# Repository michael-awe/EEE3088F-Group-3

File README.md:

# EEE3088F Project (Group 3)

This GitHub repository contains the source code and documentation for a sound and proximity light sensing HAT (Hardware Attached on Top) designed for an STM32F05C6T6 Discovery board. The repository contains detailed technical documentation with diagrams, schematics and specifications for the HAT's hardware and software.

## Project Description
Our HAT (Hardware Attached on Top) is a compact device that incorporates light proximity sensor and a sound sensor, making it an all-in-one solution for non-contact detection and monitoring. Designed to work seamlessly with STM 32 microcontrollers, the HAT offers both motion and sound sensing capabilities that make it an ideal choice for a wide range of use cases such as process monitoring, home automation, surveillance, and non-contact activation.  
With an onboard battery, the HAT can operate remotely for extended periods, providing reliable and accurate data capture during load-shedding. The HAT's data capture capabilities are enhanced by its micro-USB data transfer, which allows users to easily power the microcontroller and transfer data between it and a computer. Overall, the HAT is an excellent option for businesses and organizations looking for a cost-effective, reliable, and adaptable solution for non-contact detection and monitoring. 

## Team Members
1. Michael Awe (Microcontroller interfacing + Coding)
2. Adrian Mc Intosh (Sensor Module)
3. Simon Carthew (Power Module)

## License

This repository is licensed under the Creative Commons Attribution 4.0 International license. See `LICENSE.md` for more information.

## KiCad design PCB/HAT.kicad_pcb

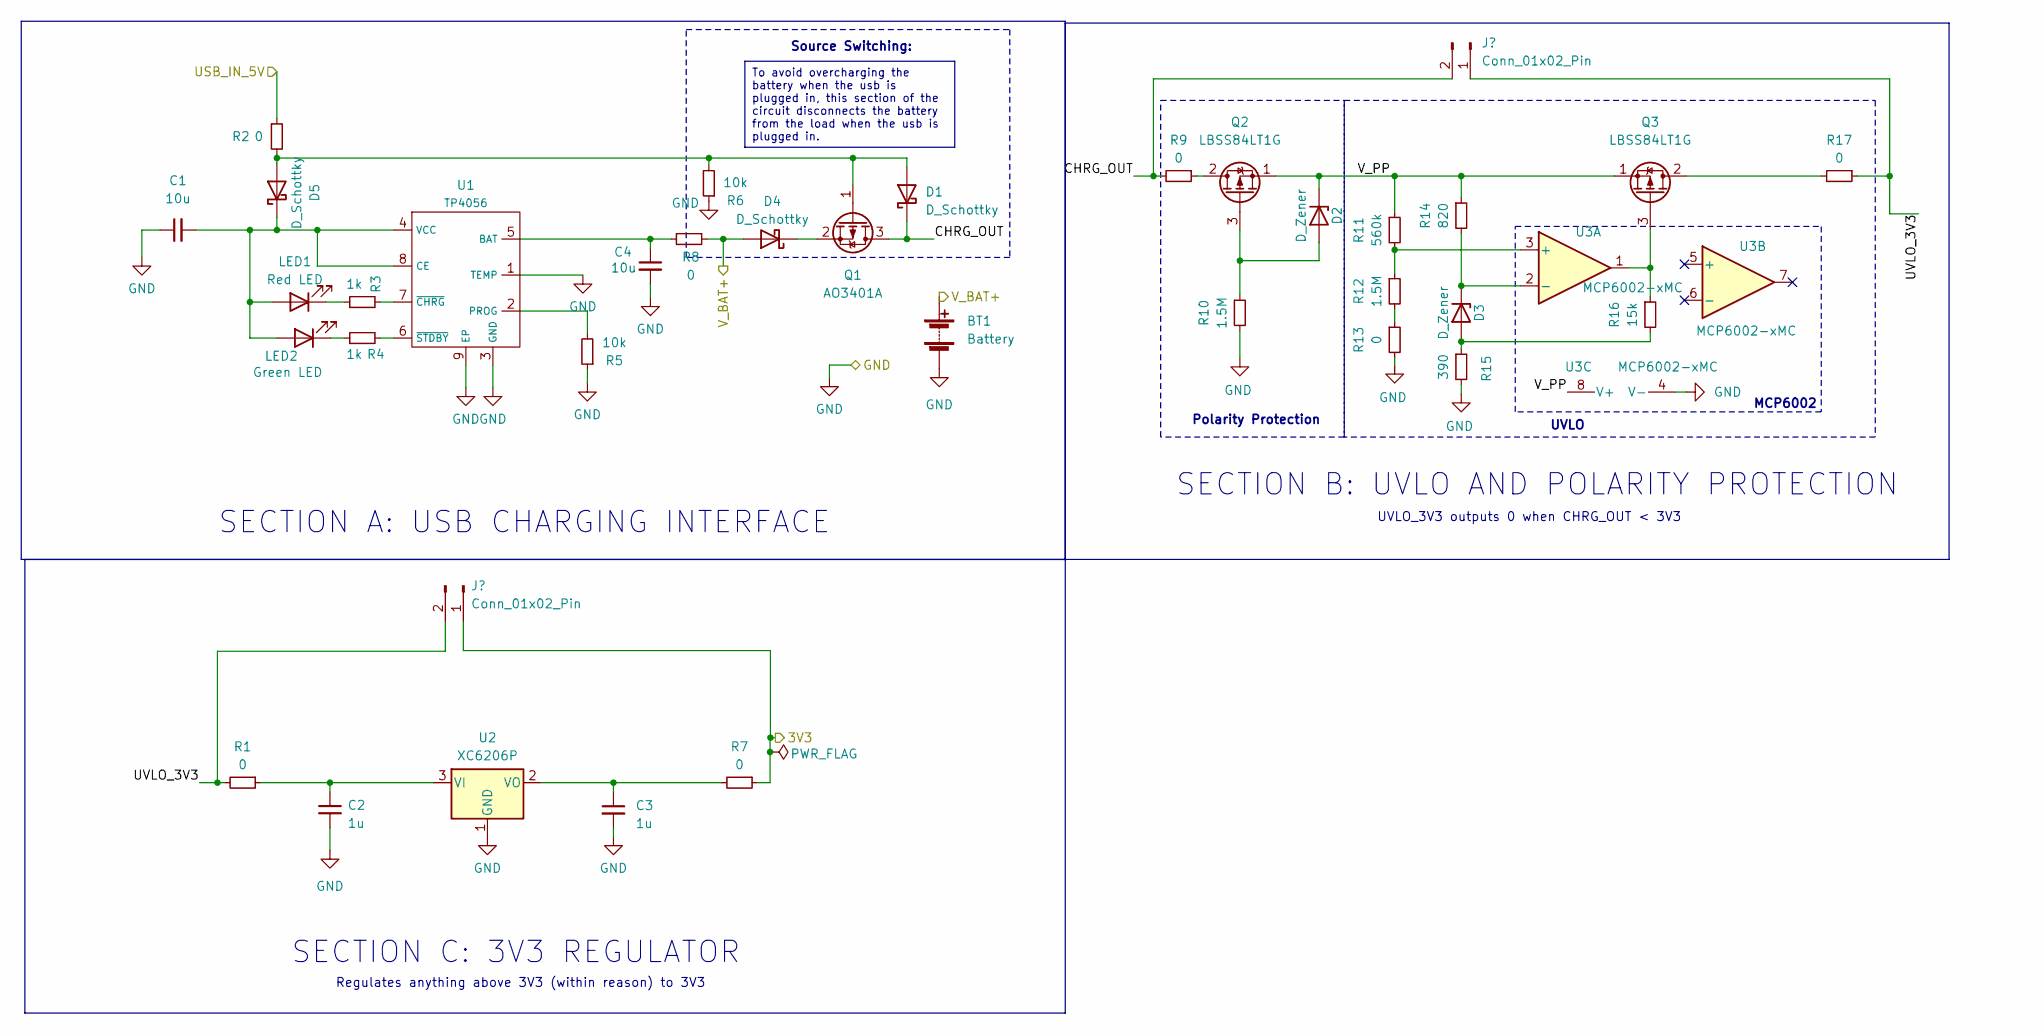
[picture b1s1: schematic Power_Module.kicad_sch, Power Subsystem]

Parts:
BT1: Battery; 18650_Holder_SMD
C1, C4: 10u; CAP-SMD_L3.2-W1.6-RD-C7171
C2, C3: 1u; C0402_NEW
D1, D4, D5: D_Schottky; SOD-323_L1.8-W1.3-LS2.5-RD
D2, D3: D_Zener; LL-34_L3.5-W1.5-RD
J1, J2: Conn_01x02_Pin; PinHeader_1x02_P2.54mm_Vertical
LED1: Red LED; LED0603-RD
LED2: Green LED; LED0805-R-RD
Q1: AO3401A; SOT-23
Q2, Q3: LBSS84LT1G; SOT-23_L2.9-W1.3-P1.90-LS2.4-BR
R1, R2, R7, R8, R9, R13, R17: 0; R_0805_2012Metric
R3, R4: 1k; R_0805_2012Metric
R5, R6: 10k; R_0805_2012Metric
R10: 1.5M; R_0805_2012Metric
R11: 560k; R_0603_1608Metric
R12: 1.5M; R_0603_1608Metric
R14: 820; R_0805_2012Metric
R15: 390; R_0805_2012Metric
R16: 15k; R_0805_2012Metric
U1: TP4056; SOIC-8-1EP_3.9x4.9mm_P1.27mm_EP2.29x3mm
U2: XC6206P; SOT-23-3
U3: MCP6002-xMC; DFN-8-1EP_3x2mm_P0.5mm_EP1.75x1.45mm

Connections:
/MicroController_Interfacing/3V3: J1.1, R7.1; also elsewhere on the board
/MicroController_Interfacing/USB 5V: R2.1; also elsewhere on the board
/Power Module/CHRG_OUT: D1.1 (K), J2.2, Q1.3 (D), R9.2
/Power Module/UVLO_3V3: J1.2, J2.1, R1.2, R17.1
/Power Module/V_BAT+: BT1.1 (+), D4.2 (A), R8.1; also elsewhere on the board
/Power Module/V_PP: D2.1 (K), Q2.1 (S), Q3.1 (S), R11.1, R14.1, U3.8 (V+)
GND: BT1.2 (-), C1.1, C2.2, C3.2, C4.2, R5.1, R6.1, R10.2, R13.2, R15.2, U1.1 (TEMP), U1.3 (GND), U1.9 (EP), U2.1 (GND), U3.4 (V-), U3.9 (V-); also elsewhere on the board
unnamed: D1.2 (A), D5.2 (A), Q1.1 (G), R2.2, R6.2
unnamed: D2.2 (A), Q2.3 (G), R10.1
unnamed: D3.2 (A), R15.1, R16.2
unnamed: D3.1 (K), R14.2, U3.2 (-)
unnamed: D4.1 (K), Q1.2 (S)
unnamed: C1.2, D5.1 (K), LED1.2 (A), LED2.2 (A), U1.4 (VCC), U1.8 (CE)
unnamed: LED1.1 (K), R3.1
unnamed: LED2.1 (K), R4.1
unnamed: Q2.2 (D), R9.1
unnamed: Q3.2 (D), R17.2
unnamed: Q3.3 (G), R16.1, U3.1
unnamed: R12.2, R13.1
unnamed: C4.1, R8.2, U1.5 (BAT)
unnamed: R5.2, U1.2 (PROG)
unnamed: R3.2, U1.7 (~CHRG)
unnamed: R4.2, U1.6 (~STDBY)
unnamed: C2.1, R1.1, U2.3 (VI)
unnamed: C3.1, R7.2, U2.2 (VO)
unnamed: R11.2, R12.1, U3.3 (+)

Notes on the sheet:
To avoid overcharging the battery when the usb is plugged in, this section of the circuit disconnects the battery from the load when the usb is plugged in.
Source Switching:
MCP6002
SECTION C: 3V3 REGULATOR
UVLO
SECTION B: UVLO AND POLARITY PROTECTION
SECTION A: USB CHARGING INTERFACE
UVLO_3V3 outputs 0 when CHRG_OUT < 3V3
Regulates anything above 3V3 (within reason) to 3V3
Polarity Protection

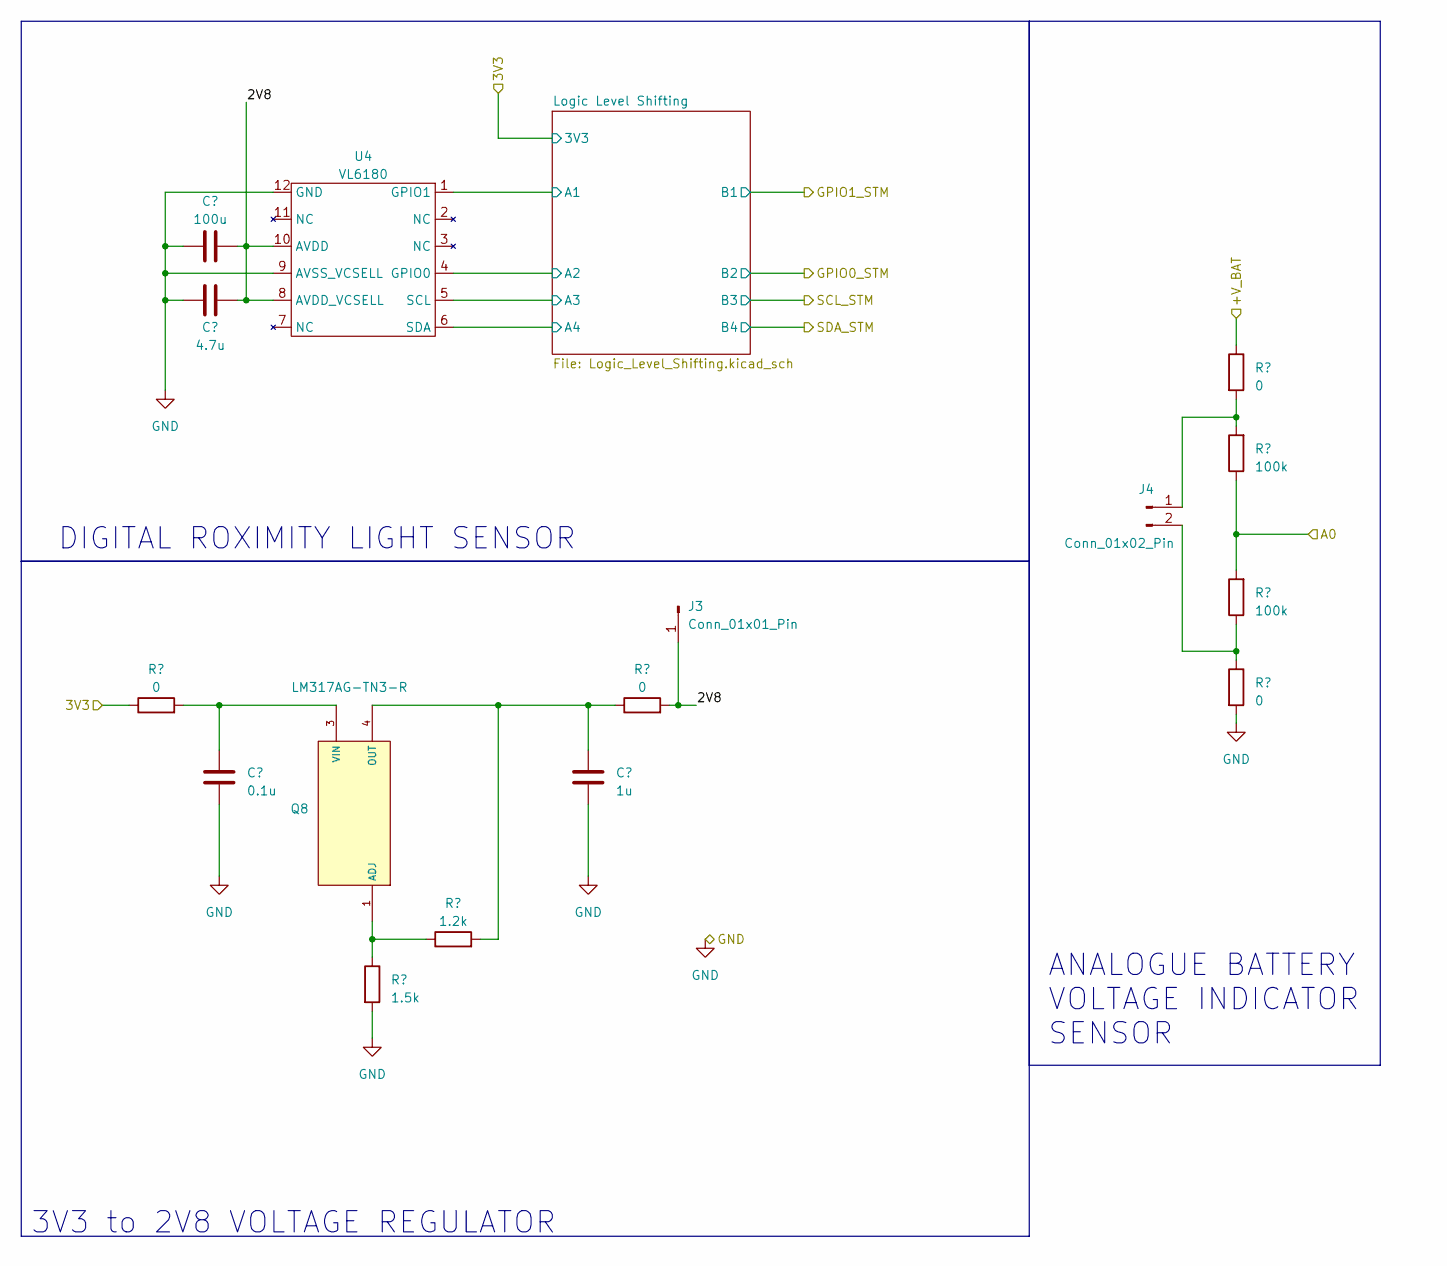
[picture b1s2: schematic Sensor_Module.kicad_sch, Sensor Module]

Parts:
C6: 100u; C1206
C7: 4.7u; C0603
C8: 0.1u; C0805
C9: 1u; C0402_NEW
J3: Conn_01x01_Pin; PinHeader_1x01_P2.54mm_Vertical
J4: Conn_01x02_Pin; PinHeader_1x02_P2.54mm_Vertical
Q8: LM317AG-TN3-R; TO-252-2_L6.5-W6.1-P4.58-LS10.0-TL; LCSC C75510
R18, R21, R22, R25: 0; R_0805_2012Metric
R19: 1.5k; R_0805_2012Metric
R20: 1.2k; R_0805_2012Metric
R23, R24: 100k; R_0805_2012Metric
U4: VL6180; LGA-12_L4.8-W2.8-P0.75-BL

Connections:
/MicroController_Interfacing/3V3: R18.1; also elsewhere on the board
/MicroController_Interfacing/A0: R23.1, R24.2; also elsewhere on the board
/Power Module/V_BAT+: R22.1; also elsewhere on the board
/Sensor Module/2V8: C6.1, C7.1, J3.1, R21.2, U4.8 (AVDD_VCSELL), U4.10 (AVDD)
/Sensor Module/Logic Level Shifting/A1: U4.1 (GPIO1); also elsewhere on the board
/Sensor Module/Logic Level Shifting/A2: U4.4 (GPIO0); also elsewhere on the board
/Sensor Module/Logic Level Shifting/A3: U4.5 (SCL); also elsewhere on the board
/Sensor Module/Logic Level Shifting/A4: U4.6 (SDA); also elsewhere on the board
GND: C6.2, C7.2, C8.1, C9.1, R19.2, R25.2, U4.9 (AVSS_VCSELL), U4.12 (GND); also elsewhere on the board
unnamed: J4.1, R22.2, R23.2
unnamed: J4.2, R24.1, R25.1
unnamed: Q8.1 (ADJ), R19.1, R20.1
unnamed: C9.2, Q8.4 (OUT), R20.2, R21.1
unnamed: C8.2, Q8.3 (VIN), R18.2

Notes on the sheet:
ANALOGUE BATTERY VOLTAGE INDICATOR SENSOR
DIGITAL ROXIMITY LIGHT SENSOR
3V3 to 2V8 VOLTAGE REGULATOR

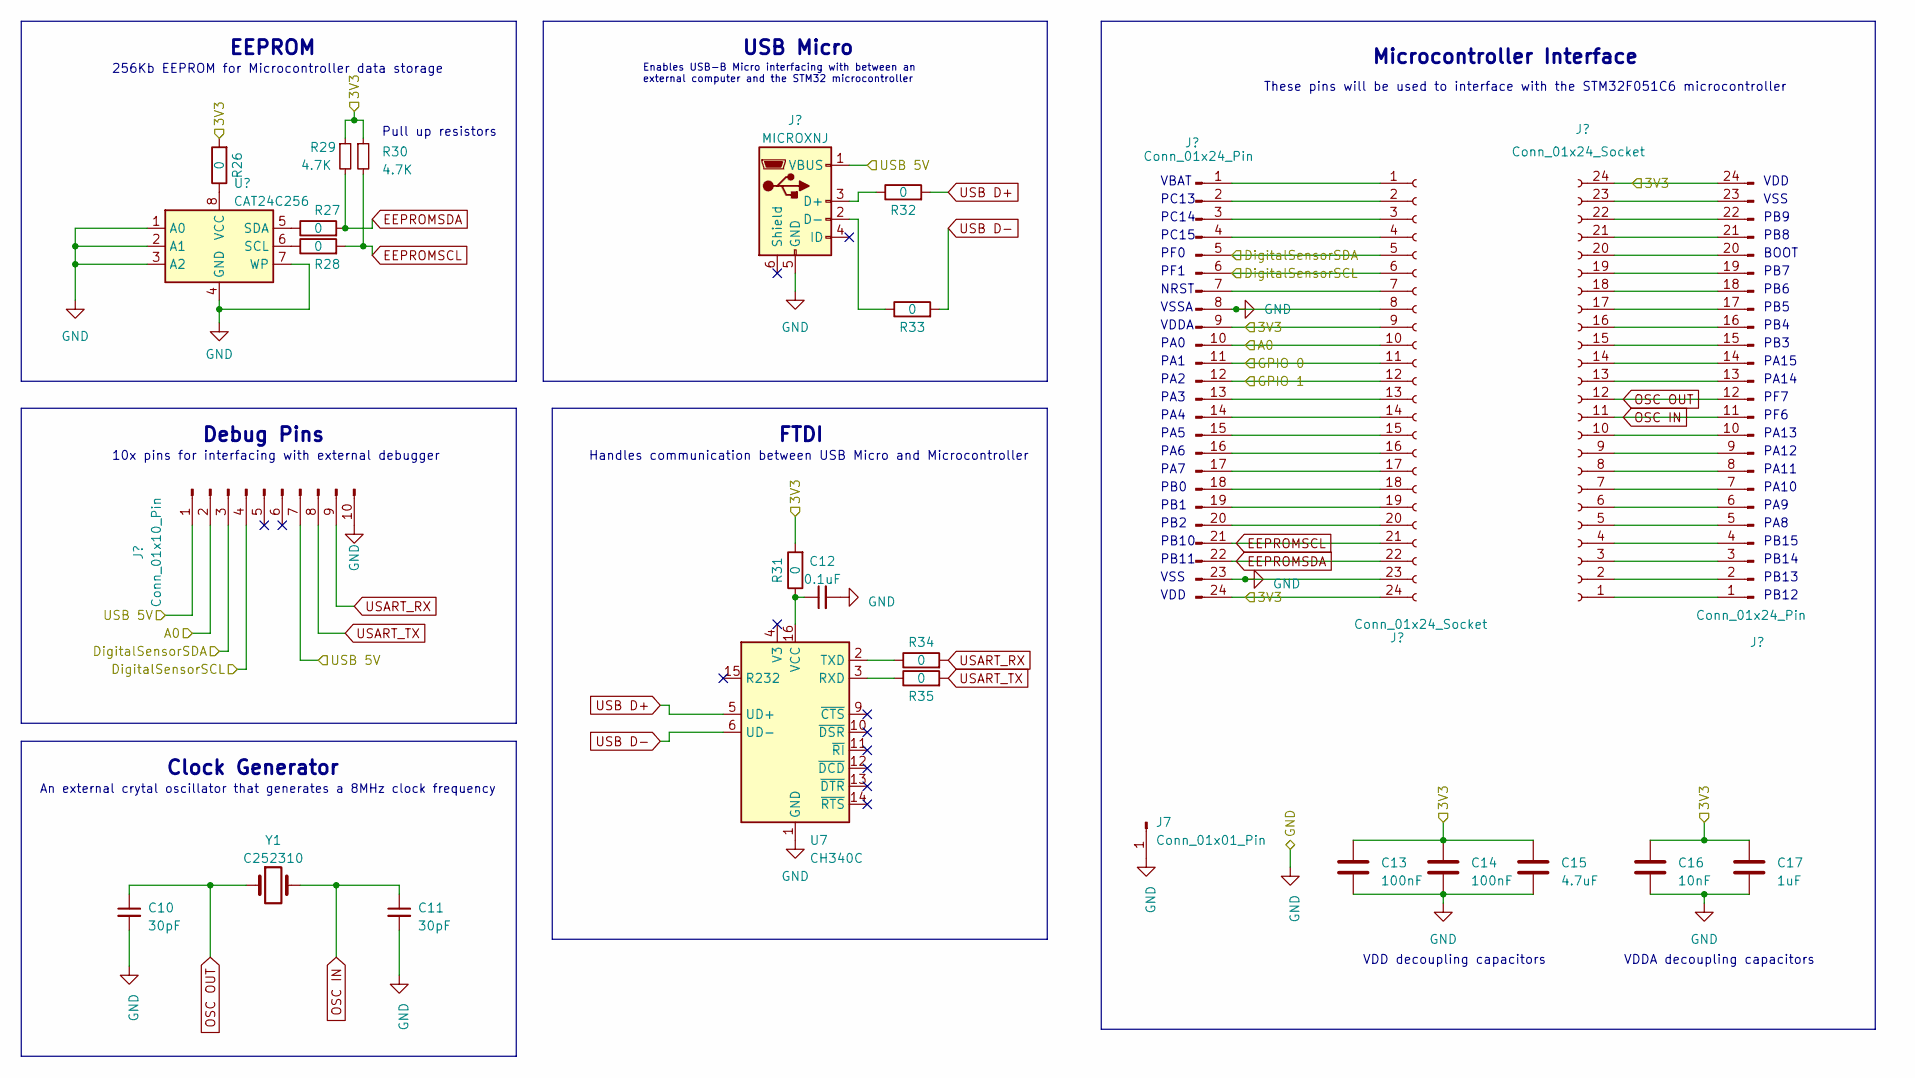
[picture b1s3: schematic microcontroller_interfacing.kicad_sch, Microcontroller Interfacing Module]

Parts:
C10, C11: 30pF; C0805
C12: 0.1uF; C0805
C13, C14: 100nF; C0402
C15: 4.7uF; C0603
C16: 10nF; C0402_NEW
C17: 1uF; C0402_NEW
J5: Conn_01x10_Pin; PinHeader_1x10_P2.54mm_Vertical
J6: MICROXNJ; USB_Conn_JLC_LCSC_C404969
J7: Conn_01x01_Pin; PinHeader_1x01_P2.54mm_Vertical
J8, J11: Conn_01x24_Pin; PinHeader_1x24_P2.54mm_Vertical
J9, J10: Conn_01x24_Socket; PinSocket_1x24_P2.54mm_Vertical
R26, R27, R28, R31, R32, R33, R34, R35: 0; R_0805_2012Metric
R29, R30: 4.7K; R_0805_2012Metric
U6: CAT24C256; SOIC-8_L4.9-W3.9-P1.27-LS6.0-BL
U7: CH340C; SOIC-16_3.9x9.9mm_P1.27mm
Y1: C252310; HC-49S_L11.4-W4.8

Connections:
/MicroController_Interfacing/3V3: C13.1, C14.1, C15.1, C16.1, C17.1, J8.9, J8.24, J9.9, J9.24, J10.24, J11.24, R26.2, R29.1, R30.1, R31.2; also elsewhere on the board
/MicroController_Interfacing/A0: J5.2, J8.10, J9.10; also elsewhere on the board
/MicroController_Interfacing/DigitalSensorSCL: J5.4, J8.6, J9.6; also elsewhere on the board
/MicroController_Interfacing/DigitalSensorSDA: J5.3, J8.5, J9.5; also elsewhere on the board
/MicroController_Interfacing/GPIO 0: J8.11, J9.11; also elsewhere on the board
/MicroController_Interfacing/GPIO 1: J8.12, J9.12; also elsewhere on the board
/MicroController_Interfacing/USB 5V: J5.1, J5.7, J6.1 (VBUS); also elsewhere on the board
EEPROMSCL: J8.21, J9.21, R28.2, R30.2
EEPROMSDA: J8.22, J9.22, R27.2, R29.2
GND: C10.2, C11.2, C12.2, C13.2, C14.2, C15.2, C16.2, C17.2, J5.10, J6.5 (GND), J7.1, J8.8, J8.23, J9.8, J9.23, U6.1 (A0), U6.2 (A1), U6.3 (A2), U6.4 (GND), U6.7 (WP), U7.1 (GND); also elsewhere on the board
unnamed: J6.3 (D+), R32.1
unnamed: J6.2 (D-), R33.1
unnamed: J8.1, J9.1
unnamed: J8.2, J9.2
unnamed: J8.3, J9.3
unnamed: J8.4, J9.4
unnamed: J8.7, J9.7
unnamed: J8.13, J9.13
unnamed: J8.14, J9.14
unnamed: J8.15, J9.15
unnamed: J8.16, J9.16
unnamed: J8.17, J9.17
unnamed: J8.18, J9.18
unnamed: J8.19, J9.19
unnamed: J8.20, J9.20
unnamed: J10.1, J11.1
unnamed: J10.2, J11.2
unnamed: J10.3, J11.3
unnamed: J10.4, J11.4
unnamed: J10.5, J11.5
unnamed: J10.6, J11.6
unnamed: J10.7, J11.7
unnamed: J10.8, J11.8
unnamed: J10.9, J11.9
unnamed: J10.10, J11.10
unnamed: J10.13, J11.13
unnamed: J10.14, J11.14
unnamed: J10.15, J11.15
unnamed: J10.16, J11.16
unnamed: J10.17, J11.17
unnamed: J10.18, J11.18
unnamed: J10.19, J11.19
unnamed: J10.20, J11.20
unnamed: J10.21, J11.21
unnamed: J10.22, J11.22
unnamed: J10.23, J11.23
unnamed: R28.1, U6.6 (SCL)
unnamed: R27.1, U6.5 (SDA)
unnamed: R26.1, U6.8 (VCC)
unnamed: R35.1, U7.3 (RXD)
unnamed: R34.1, U7.2 (TXD)
unnamed: C12.1, R31.1, U7.16 (VCC)
OSC IN: C11.1, J10.11, J11.11, Y1.2
OSC OUT: C10.1, J10.12, J11.12, Y1.1
USART_RX: J5.9, R34.2
USART_TX: J5.8, R35.2
USB D+: R32.2, U7.5 (UD+)
USB D-: R33.2, U7.6 (UD-)

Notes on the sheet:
BOOT
PA4
PB6
PA14
PB3
PA2
Microcontroller Interface
PB10
VSSA
VSS
VDD
VBAT
PC13
PF1
PA11
Clock Generator
256Kb EEPROM for Microcontroller data storage
NRST
10x pins for interfacing with external debugger
PA12
PF0
VDDA
USB Micro
PB0
PA8
PA13
PA15
PA7
PA9
Pull up resistors
PA5
PC15
These pins will be used to interface with the STM32F051C6 microcontroller
PB4
PA3
PB11
Handles communication between USB Micro and Microcontroller
PB12
PC14
An external crytal oscillator that generates a 8MHz clock frequency

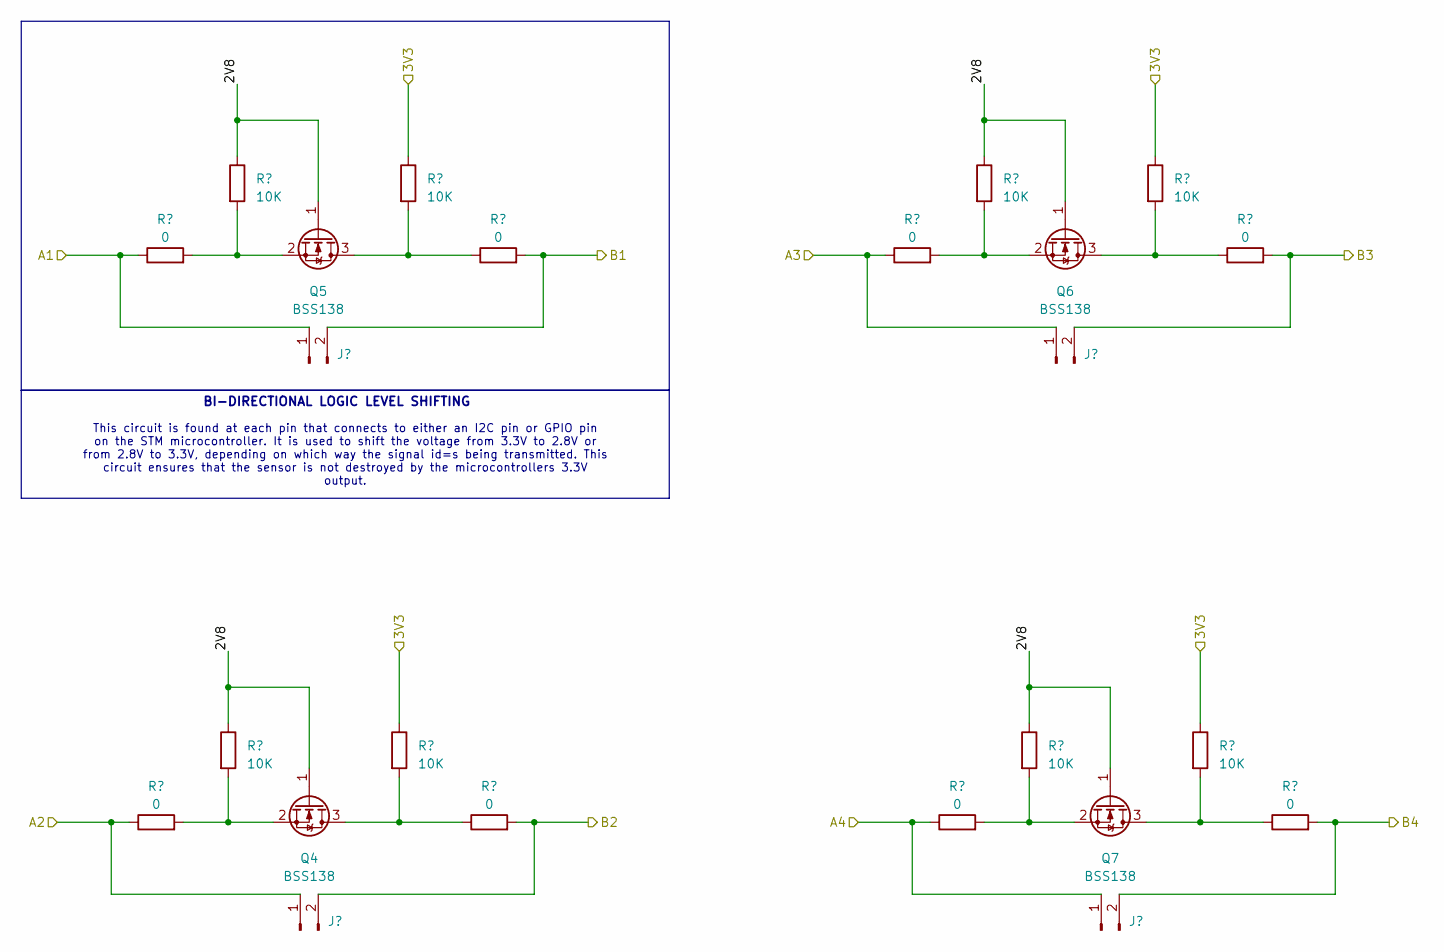
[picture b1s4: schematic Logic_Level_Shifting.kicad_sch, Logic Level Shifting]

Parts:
J12, J13, J14, J15: Conn_01x02_Pin; PinHeader_1x02_P2.54mm_Vertical
Q4, Q5, Q6, Q7: BSS138; SOT-23-3_L2.9-W1.3-P1.90-LS2.4-BR
R36, R37, R42, R43, R44, R45, R50, R51: 0; R_0805_2012Metric
R38, R39, R40, R41, R46, R47, R48, R49: 10K; R_0805_2012Metric

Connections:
/MicroController_Interfacing/3V3: R40.1, R41.1, R48.1, R49.1; also elsewhere on the board
/MicroController_Interfacing/DigitalSensorSCL: J14.2, R50.2; also elsewhere on the board
/MicroController_Interfacing/DigitalSensorSDA: J15.2, R51.2; also elsewhere on the board
/MicroController_Interfacing/GPIO 0: J12.2, R42.2; also elsewhere on the board
/MicroController_Interfacing/GPIO 1: J13.2, R43.2; also elsewhere on the board
/Sensor Module/Logic Level Shifting/2V8: Q4.1 (G), Q5.1 (G), Q6.1 (G), Q7.1 (G), R38.1, R39.1, R46.1, R47.1
/Sensor Module/Logic Level Shifting/A1: J13.1, R37.1; also elsewhere on the board
/Sensor Module/Logic Level Shifting/A2: J12.1, R36.1; also elsewhere on the board
/Sensor Module/Logic Level Shifting/A3: J14.1, R44.1; also elsewhere on the board
/Sensor Module/Logic Level Shifting/A4: J15.1, R45.1; also elsewhere on the board
unnamed: Q4.3 (D), R40.2, R42.1
unnamed: Q4.2 (S), R36.2, R38.2
unnamed: Q5.3 (D), R41.2, R43.1
unnamed: Q5.2 (S), R37.2, R39.2
unnamed: Q6.3 (D), R48.2, R50.1
unnamed: Q6.2 (S), R44.2, R46.2
unnamed: Q7.3 (D), R49.2, R51.1
unnamed: Q7.2 (S), R45.2, R47.2

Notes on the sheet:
This circuit is found at each pin that connects to either an I2C pin or GPIO pin on the STM microcontroller. It is used to shift the voltage from 3.3V to 2.8V or from 2.8V to 3.3V, depending on which way the signal id=s being transmitted. This circuit ensures that the sensor is not destroyed by the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
BI-DIRECTIONAL LOGIC LEVEL SHIFTING

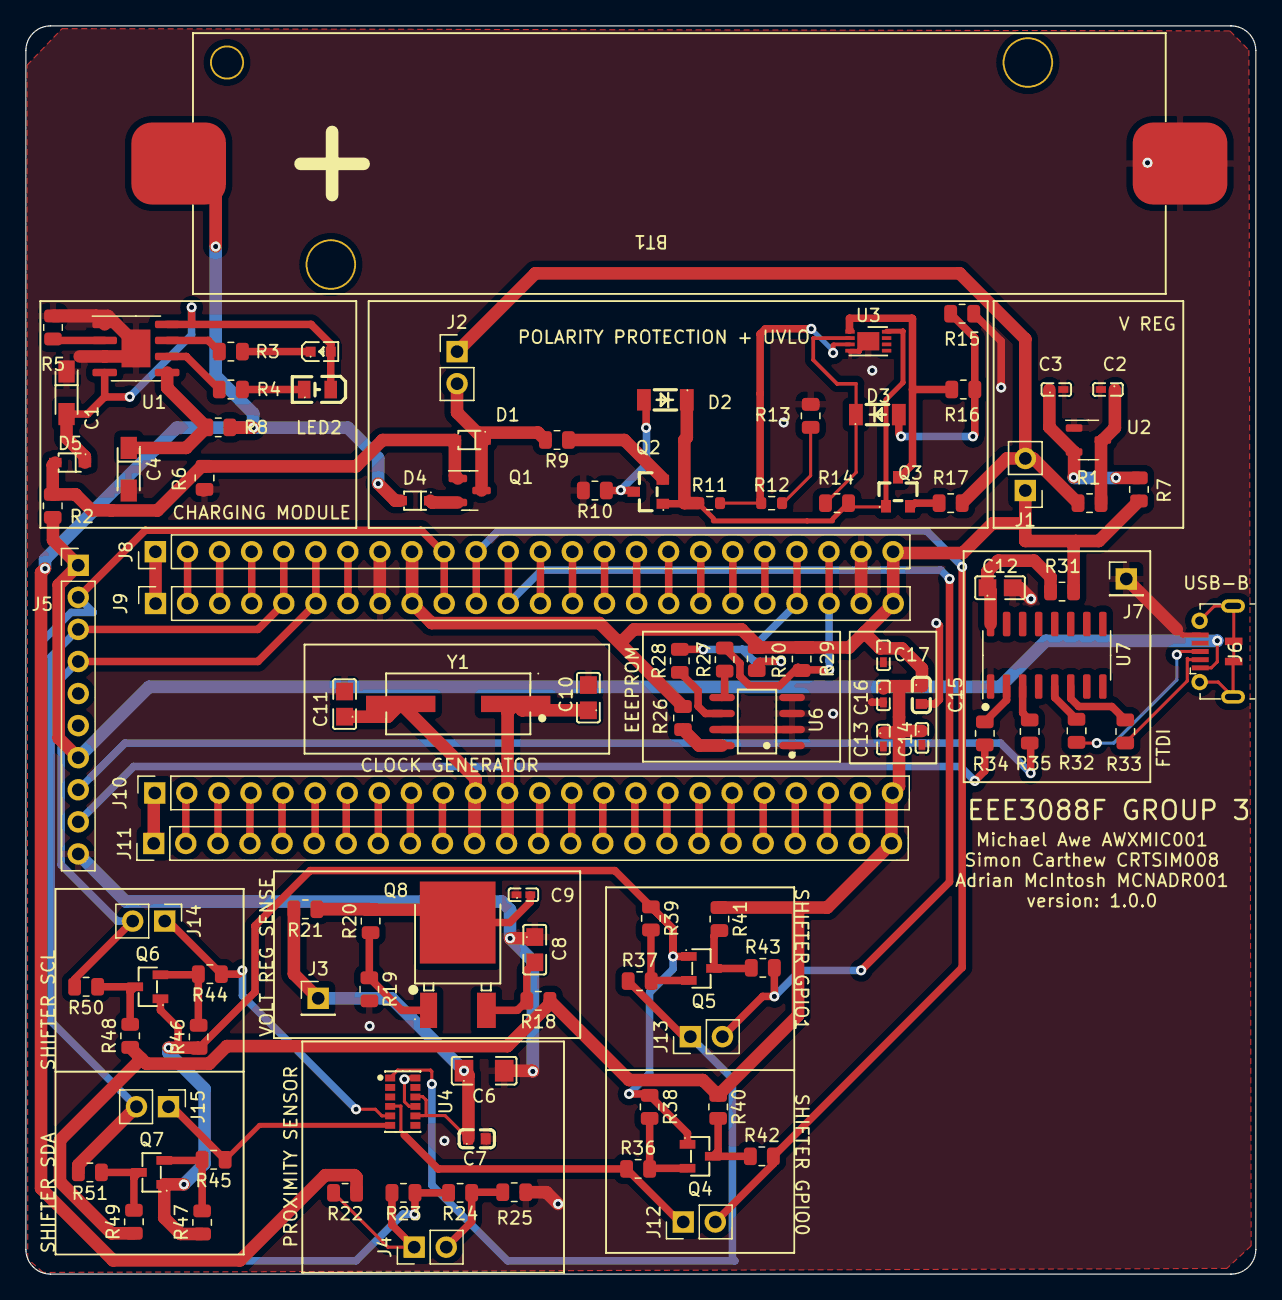
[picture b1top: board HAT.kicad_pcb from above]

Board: 2 copper layers, 97.4 x 98.8 mm, 105 parts (0 on the bottom side), 100 nets.

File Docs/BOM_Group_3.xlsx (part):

JLCPCB PART NUM | MANUFACTURER PART NO. | EXTENDED PART | JLCPCB PART LINK | KICAD SCHEMATIC REFERENCE | COMPONENT VALUE | QTY PER BOARD | QTY FIVE BOARDS | PRICE PER UNIT ($) | PRICE PER BOARD ($) | PRIVE FIVE BOARDS ($) | PRICE FIVE BOARDS EXTENDED ($)
C15008 | CC0805KRX7R9BB104 | 0 | https://jlcpcb.com/partdetail/15681-CL31A107MQHNNNE/C15008 | C6 | 100u | 1 | 5 | 4.5999999999999999E-3 | 4.5999999999999999E-3 | 2.3E-2 | 2.3E-2 |  |  |  | SENSOR MODULE TOTALS
C28323 | CL21B105KBFNNNE | 0 | https://jlcpcb.com/partdetail/29074-CL21B105KBFNNNE/C28323 | C7 | 4.7u | 1 | 15 | 9.4999999999999998E-3 | 9.4999999999999998E-3 | 0.14249999999999999 | 0.14249999999999999 |  |  |  | One Board | 3.6037999899999997
C149504 | 0805W8F1003T5E | 0 | https://jlcpcb.com/partdetail/160838-0805W8F1003T5E/C149504 | R23,R24 | 100k | 2 | 10 | 1.6999999999999999E-3 | 3.3999999999999998E-3 | 1.6999999999999998E-2 | 1.6999999999999998E-2 |  |  |  | Five Boards | 18.018999949999998
C4310 | 0805W8F1501T5E | 0 | https://jlcpcb.com/partdetail/4717-0805W8F1501T5E/C4310 | 19 | 1.5k | 1 | 5 | 1.8E-3 | 1.8E-3 | 8.9999999999999993E-3 | 8.9999999999999993E-3
C17379 | 0805W8F1201T5E | 0 | https://jlcpcb.com/partdetail/18067-0805W8F1201T5E/C17379 | 20 | 1.2k | 1 | 5 | 1.8E-3 | 1.8E-3 | 8.9999999999999993E-3 | 8.9999999999999993E-3 |  |  |  | MICROCONTROLLER MODULE TOTALS
C2655167 | VL6180V1NR/1 | 1 | https://test.jlcpcb.com/partdetail/Stmicroelectronics-VL6180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 | VL6180 | PROX SENSOR | 1 | 5 | 2.0785999999999998 | 2.0785999999999998 | 10.392999999999999 | 13.392999999999999 |  |  |  | One Board | 3.5442
C75510 | LM317AG-TN3-R | 0 | https://jlcpcb.com/partdetail/utc_unisonic_tech-LM317AG_TN3R/C75510 | Q8 | LM317AG | 1 | 5 | 0.18720000000000001 | 0.18720000000000001 | 0.93600000000000005 | 0.93600000000000005 |  |  |  | Five Boards | 17.721
C78284 | BSS138 | 1 | https://jlcpcb.com/partdetail/79418-BSS138/C78284 | Q4, Q6, Q7, Q8 | BSS138 | 4 | 15 | 2.2499999999999999E-2 | 0.09 | 0.33749999999999997 | 3.3374999999999999
C17414 | 0805W8F1002T5E | 0 | 0805W8F1002T5E | UNI-ROYAL(Uniroyal Elec) | Chip Resistor - Surface Mount | JLC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 | R38, R39, R40, R41, R46, R47, R48, R49 | 10k | 8 | 15 | 1.33333E-3 | 1.066664E-2 | 1.9999949999999999E-2 | 1.9999949999999999E-2
C17477 | 0805W8F0000T5E | 0 | https://jlcpcb.com/partdetail/18165-0805W8F0000T5E/C17477 | R18,R21,R22,R25,R37,R43,R44,R50,R36,R42,R45,R51 | 0k | 12 | 60 | 2.2000000000000001E-3 | 2.64E-2 | 0.13200000000000001 | 0.13200000000000001 |  |  |  | POWER MODULE TOTALS
 |  |  |  |  |  |  |  |  |  |  |  |  |  |  | One Board | 1.2916666600000002
 |  |  |  |  |  |  |  |  |  |  |  |  |  |  | Five Boards | 9.4583333000000014
JLCPCB PART NUM | MANUFACTURER PART NO. | EXTENDED PART | JLCPCB PART LINK | KICAD SCHEMATIC REFERENCE | COMPONENT VALUE | QTY PER BOARD | QTY FIVE BOARDS | PRICE PER UNIT ($) | PRICE PER BOARD ($) | PRIVE FIVE BOARDS ($) | PRICE FIVE BOARDS EXTENDED ($)
C7171 | TAJA106K016RNJ | 0 | https://jlcpcb.com/partdetail/KyoceraAvx-TAJA106K016RNJ/C7171 | C1, C4 | 10uF | 2 | 10 | 8.7999999999999995E-2 | 0.17599999999999999 | 0.87999999999999989 | 0.87999999999999989
C49678 | CC0805KRX7R9BB104 | 0 | https://jlcpcb.com/partdetail/Yageo-CC0805KRX7R9BB104/C49678 | C8 | 0.1u | 1 | 5 | 4.5999999999999999E-3 | 4.5999999999999999E-3 | 2.3E-2 | 2.3E-2 |  |  |  | HAT TOTALS
C2286 | KT-0603R | 0 | https://jlcpcb.com/partdetail/Hubei_KentoElec-KT0603R/C2286 | LED1 | Red LED | 1 | 5 | 6.0000000000000001E-3 | 6.0000000000000001E-3 | 0.03 | 0.03 |  |  |  | Sensor Module | 18.018999949999998
C2297 | C2297 | 0 | https://jlcpcb.com/partdetail/Hubei_KentoElec-C2297/C2297 | LED2 | Green LED | 1 | 5 | 1.3299999999999999E-2 | 1.3299999999999999E-2 | 6.6500000000000004E-2 | 6.6500000000000004E-2 |  |  |  | Power Module | 9.4583333000000014
C17414 | 0805W8F1002T5E | 0 | https://jlcpcb.com/partdetail/18102-0805W8F1002T5E/C17414 | R5, R6 | 10k | 2 | 10 | 1.33333E-3 | 2.66666E-3 | 1.3333299999999999E-2 | 1.3333299999999999E-2 |  |  |  | MicroController Interfacing | 17.721
C17477 | 0805W8F0000T5E | 0 | https://jlcpcb.com/partdetail/18165-0805W8F0000T5E/C17477 | R1, R2, R7, R8, R9, R17 | 0k | 6 | 30 | 2.2000000000000001E-3 | 1.32E-2 | 6.6000000000000003E-2 | 6.6000000000000003E-2 |  |  |  | Manufacturing | 12
C17927 | C17927 | 0 | https://jlcpcb.com/partdetail/18615-1206W4F1004T5E/C17927 | R11, R13 | 1M | 2 | 10 | 3.0999999999999999E-3 | 6.1999999999999998E-3 | 3.1E-2 | 3.1E-2 |  |  |  | GRAND TOTAL | 57.198333250000005
C17927 | GZ2012D101TF | 0 | https://jlcpcb.com/partdetail/Sunlord-GZ2012D101TF/C1015 | R15, R16 | 100 | 2 | 10 | 9.4000000000000004E-3 | 1.8800000000000001E-2 | 9.4E-2 | 9.4E-2
C2857251 | ZMM2V0 | 1 | https://jlcpcb.com/partdetail/Jsmsemi-ZMM2V0/C2857251 | D2, D3 | D_Zener | 1 | 5 | 1.03E-2 | 1.03E-2 | 5.1500000000000004E-2 | 3.0514999999999999
C4172 | 0603WAF1504T5E | 0 | https://jlcpcb.com/partdetail/4579-0603WAF1504T5E/C4172 | R10, R11 | 1.5M | 2 | 10 | 1.6999999999999999E-3 | 3.3999999999999998E-3 | 1.6999999999999998E-2 | 1.6999999999999998E-2
C22764 | 0603WAF1101T5E | 0 | https://jlcpcb.com/partdetail/23491-0603WAF1101T5E/C22764 | R3, R4, R14 | 1k | 3 | 15 | 2E-3 | 6.0000000000000001E-3 | 0.03 | 0.03
C191023 | 1N5819WS | 0 | https://jlcpcb.com/partdetail/GuangdongHottech-1N5819WS/C191023 | D1, D2 | 1N5819 | 2 | 10 | 0.16200000000000001 | 0.32400000000000001 | 1.62 | 1.62
C7433 | OP07CDR | 0 | https://jlcpcb.com/partdetail/TexasInstruments-OP07CDR/C7433 | U3 | OP07 | 1 | 5 | 0.28000000000000003 | 0.28000000000000003 | 1.4000000000000001 | 1.4000000000000001
C8492 | LBSS84LT1G | 0 | https://jlcpcb.com/partdetail/Lrc-LBSS84LT1G/C8492 | Q2, Q3 | LBSS84LT1G | 2 | 10 | 2.4199999999999999E-2 | 4.8399999999999999E-2 | 0.24199999999999999 | 0.24199999999999999
C5446 | XC6206P332MR | 0 | https://jlcpcb.com/partdetail/TorexSemicon-XC6206P332MR/C5446 | U2 | XC6206P | 1 | 5 | 9.64E-2 | 9.64E-2 | 0.48199999999999998 | 0.48199999999999998
C15127 | AO3401A | 0 | https://jlcpcb.com/partdetail/Alpha_OmegaSemicon-AO3401A/C15127 | Q1 | AO3401A | 1 | 5 | 7.9699999999999993E-2 | 7.9699999999999993E-2 | 0.39849999999999997 | 0.39849999999999997
C16581 | TP4056-42-ESOP8 | 0 | https://jlcpcb.com/partdetail/17264-TP4056_42ESOP8/C16581 | U1 | TP4056 | 1 | 5 | 0.20269999999999999 | 0.20269999999999999 | 1.0135000000000001 | 1.0135000000000001
JLCPCB PART NUM | MANUFACTURER PART NO. | EXTENDED PART | JLCPCB PART LINK | KICAD SCHEMATIC REFERENCE | COMPONENT VALUE | QTY PER BOARD | QTY FIVE BOARDS | PRICE PER UNIT ($) | PRICE PER BOARD ($) | PRICE FIVE BOARDS ($) | PRICE FIVE BOARDS EXTENDED ($)
C404969 | MICROXNJ | 1 | https://jlcpcb.com/partdetail/ShouHan-MicroXNJ/C404969 | J6 | Micro-B USB Connector | 1 | 5 | 0.03 | 0.03 | 0.15 | 3.15
C79987 | CAT24C256WI-GT3 | 1 | https://jlcpcb.com/partdetail/Onsemi-CAT24C256WIGT3/C79987 | U6 | EEPROM | 1 | 5 | 0.43 | 0.43 | 2.15 | 5.15
C84681 | CH340C | 1 | https://jlcpcb.com/partdetail/wch_jiangsu_Qin_heng-CH340C/C84681 | U7 | USB to Serial | 1 | 5 | 0.47 | 0.47 | 2.35 | 5.35
C17477 | 0805W8F0000T5E | 0 | https://jlcpcb.com/partdetail/18165-0805W8F0000T5E/C17477 | R26, R27, R28, R31, R32, R33, R34, R35 | 0k | 8 | 40 | 2.2000000000000001E-3 | 1.7600000000000001E-2 | 8.7999999999999995E-2 | 8.7999999999999995E-2
C49678 | CC0805KRX7R9BB104 | 0 | https://jlcpcb.com/partdetail/Yageo-CC0805KRX7R9BB104/C49678 | C12 | 0.1uF | 1 | 5 | 4.5999999999999999E-3 | 4.5999999999999999E-3 | 2.3E-2 | 2.3E-2
C23162 | 0603WAF4701T5E | 0 | https://jlcpcb.com/parts/2nd/Resistors/Chip_Resistor_Surface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 | R29, R30 | 4.7K | 2 | 10 | 1E-3 | 2E-3 | 0.01 | 0.01
C1525 | CL05B104KO5NNNC | 0 | https://jlcpcb.com/partdetail/1877-CL05B104KO5NNNC/C1525 | C13, C14 | 100nF | 2 | 10 | 0.01 | 0.02 | 0.1 | 0.1
C19666 | CL10A475KO8NNNC | 0 | https://jlcpcb.com/partdetail/20375-CL10A475KO8NNNC/C19666 | C15 | 4.7uF | 1 | 5 | 0.01 | 0.01 | 0.05 | 0.05
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
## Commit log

2023-02-26 CAD 2
2023-02-26 CAD 3
2023-02-26 IGNORE
2023-02-26 MODULES
2023-02-26 READ ME
2023-02-27 name correction
2023-03-05 SensorModuleBOM
2023-03-05 Remove
2023-03-05 SensorModule2
2023-03-06 Added microcontroller interfacing BOM
2023-03-06 Rename LICENCE.md to LICENSE.md
    Minor spelling change
2023-03-06 MicroBOM
2023-03-06 MicoBOM
2023-03-06 PowerBOM
2023-03-06 added power circuit schematic
2023-03-09 some updated changes to power circuit
2023-03-09 Made KiCAD project
2023-03-09 Deleted unnecessary xlsx file
2023-03-09 progress w/ power module schematic, updated BOM
2023-03-09 updated Power_Module_BOM
2023-03-12 Add microcontroller interfacing schematic
2023-03-12 Revert "Add microcontroller interfacing schematic"
    This reverts commit cb65be9f095c25773123ea45fc6a49ffd102fb8b.
2023-03-12 made a bunch of progress with design of UVLO and PP
2023-03-12 MERGING SCHEMATICS
2023-03-12 ANNOTATED
2023-03-12 Changed Sensor Sheet Description
2023-03-12 some small changes
2023-03-13 updated everything for Week 4 submission
2023-03-13 Merging Fixed
2023-03-13 Update MC Interfacing schematic
2023-03-13 UPDATED AND MERGED BOM
2023-03-13 Add GND jumper pin to STM-32
2023-03-13 Updated BOM
2023-03-16 Changed Sensor and added hierachiel sheet
2023-03-20 Add GPIO pins and crystal oscillator
2023-03-20 updated schematic
2023-03-20 Merging commit
2023-03-20 commenting of trace thicknesses
2023-03-20 Update MC schematic
2023-03-20 changes to schematic based on available components
2023-03-20 literally all the footprints
2023-03-20 PCB_Design_1
2023-03-20 sensor layout pcb
2023-03-20 Modified PCB
2023-03-21 DRCs done
2023-03-21 updated Gerbers!
2023-03-21 Updated BOM!
2023-04-03 Fixed via issues on PCB
2023-04-03 fixing of PCB Design
2023-04-03 Pins not Sockets
2023-04-03 Add LCSC numbers
2023-04-04 updated power cct and PCB
2023-04-04 Update BOM, position files and gerbers
2023-04-13 Final Fixes
2023-04-14 simon changes
2023-04-14 final pcb and chematic changes
2023-04-14 actual final pcb and schematic changes
2023-05-14 CONTRIBUTING.md added
2023-05-14 First Firmware
